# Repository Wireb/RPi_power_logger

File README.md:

# RPi Power Logger
These files are for my Raspberry Pi Zero based power data logger hat. 
 
License is MIT so do what you want with it just don't litigate me. 

Have had quite a few times where I needed actual run times of various battery powered devices. Built this device to collect both the battery voltage, current, and average power as well as up to 8 other voltage rails.

The simple use case is to put channel 0 in line with your battery powered device. This channel is based on the TI INA233 Bidirectional current and power sensor. It supports up to 36Vin and a wide range of currents depending on your choice for R17 and scaling factor. See the INA233 datasheet for more info. In my case of small battery powered devices I have optimized for a max current of 2A. Note the INA233 is set up for high side sensing and the RPi must be powered externally with a common ground with the circuit under test. Once inserted in the power lines just log into the Pi and start the perl script. It will generate a ./Power_data.csv file with all the readings taken every second until you kill the process. 

More advanced setups can use channels 1 - 8 to monitor internal voltage rails. I use this to see which rail is failing first and if any become unstable when the battery voltage is low. Channels 1 - 3 support up to 4V max, channles 4 - 6 support up to 6V max, and channels 7 and 8 support up to 15V max. Note all channels are on a common ground reference.

There is configuration variables in the Perl script for which channels to sample, time between samples, max sample time, and some INA233 configuration. (see Raspbian-Perl directory for more info)

## KiCad
This is a KiCad 5.1.4 project. Both the original KiCad logics, PCB files and a xlsx bill of material can be found here as well as a PDF file of the logics and a top side image of the PCB.   

## Raspbian-Perl
This is the perl script I use to collect the data on the Raspberry Pi. Sample output .csv file of just channel 0 and a processed graph in xlsx format are also included. 

Copyright (c) 2019 Peter Shabino

Permission is hereby granted, free of charge, to any person obtaining a copy of this hardware, software, and associated documentation files 
(the "Product"), to deal in the Product without restriction, including without limitation the rights to use, copy, modify, merge, publish, 
distribute, sublicense, and/or sell copies of the Product, and to permit persons to whom the Product is furnished to do so, subject to the 
following conditions:

The above copyright notice and this permission notice shall be included in all copies or substantial portions of the Product.

THE PRODUCT IS PROVIDED "AS IS", WITHOUT WARRANTY OF ANY KIND, EXPRESS OR IMPLIED, INCLUDING BUT NOT LIMITED TO THE WARRANTIES OF 
MERCHANTABILITY, FITNESS FOR A PARTICULAR PURPOSE AND NONINFRINGEMENT. IN NO EVENT SHALL THE AUTHORS OR COPYRIGHT HOLDERS BE LIABLE 
FOR ANY CLAIM, DAMAGES OR OTHER LIABILITY, WHETHER IN AN ACTION OF CONTRACT, TORT OR OTHERWISE, ARISING FROM, OUT OF OR IN CONNECTION 
WITH THE PRODUCT OR THE USE OR OTHER DEALINGS IN THE PRODUCT.

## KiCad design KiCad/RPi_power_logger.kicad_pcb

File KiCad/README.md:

# KiCad project files
These are KiCad 5.1.4 compatible files. Not going any deeper than that :)

If you just want PCBs now they are available on OSHpark here: 
https://oshpark.com/shared_projects/NPSVbO1J
<a href="https://oshpark.com/shared_projects/NPSVbO1J"></img></a>

## partnumber.csv
CSV file of all unique part numbers. (used for ordering)

## refdes.csv
CSV file of every part by refdes. (used for building)

## RPi_power_logger.xlsx
Bill of Materials in Microsoft Excel format. Includes links to Digikey. 

## RPi_power_logger.pdf
PDF file of logics for easy viewing without KiCad installed. 

## RPi_power_logger_PCB.png
Image file of the top side of the PCB and refdes for easy viewing without KiCad installed. 

Copyright (c) 2019 Peter Shabino

Permission is hereby granted, free of charge, to any person obtaining a copy of this hardware, software, and associated documentation files 
(the "Product"), to deal in the Product without restriction, including without limitation the rights to use, copy, modify, merge, publish, 
distribute, sublicense, and/or sell copies of the Product, and to permit persons to whom the Product is furnished to do so, subject to the 
following conditions:

The above copyright notice and this permission notice shall be included in all copies or substantial portions of the Product.

THE PRODUCT IS PROVIDED "AS IS", WITHOUT WARRANTY OF ANY KIND, EXPRESS OR IMPLIED, INCLUDING BUT NOT LIMITED TO THE WARRANTIES OF 
MERCHANTABILITY, FITNESS FOR A PARTICULAR PURPOSE AND NONINFRINGEMENT. IN NO EVENT SHALL THE AUTHORS OR COPYRIGHT HOLDERS BE LIABLE 
FOR ANY CLAIM, DAMAGES OR OTHER LIABILITY, WHETHER IN AN ACTION OF CONTRACT, TORT OR OTHERWISE, ARISING FROM, OUT OF OR IN CONNECTION 
WITH THE PRODUCT OR THE USE OR OTHER DEALINGS IN THE PRODUCT.

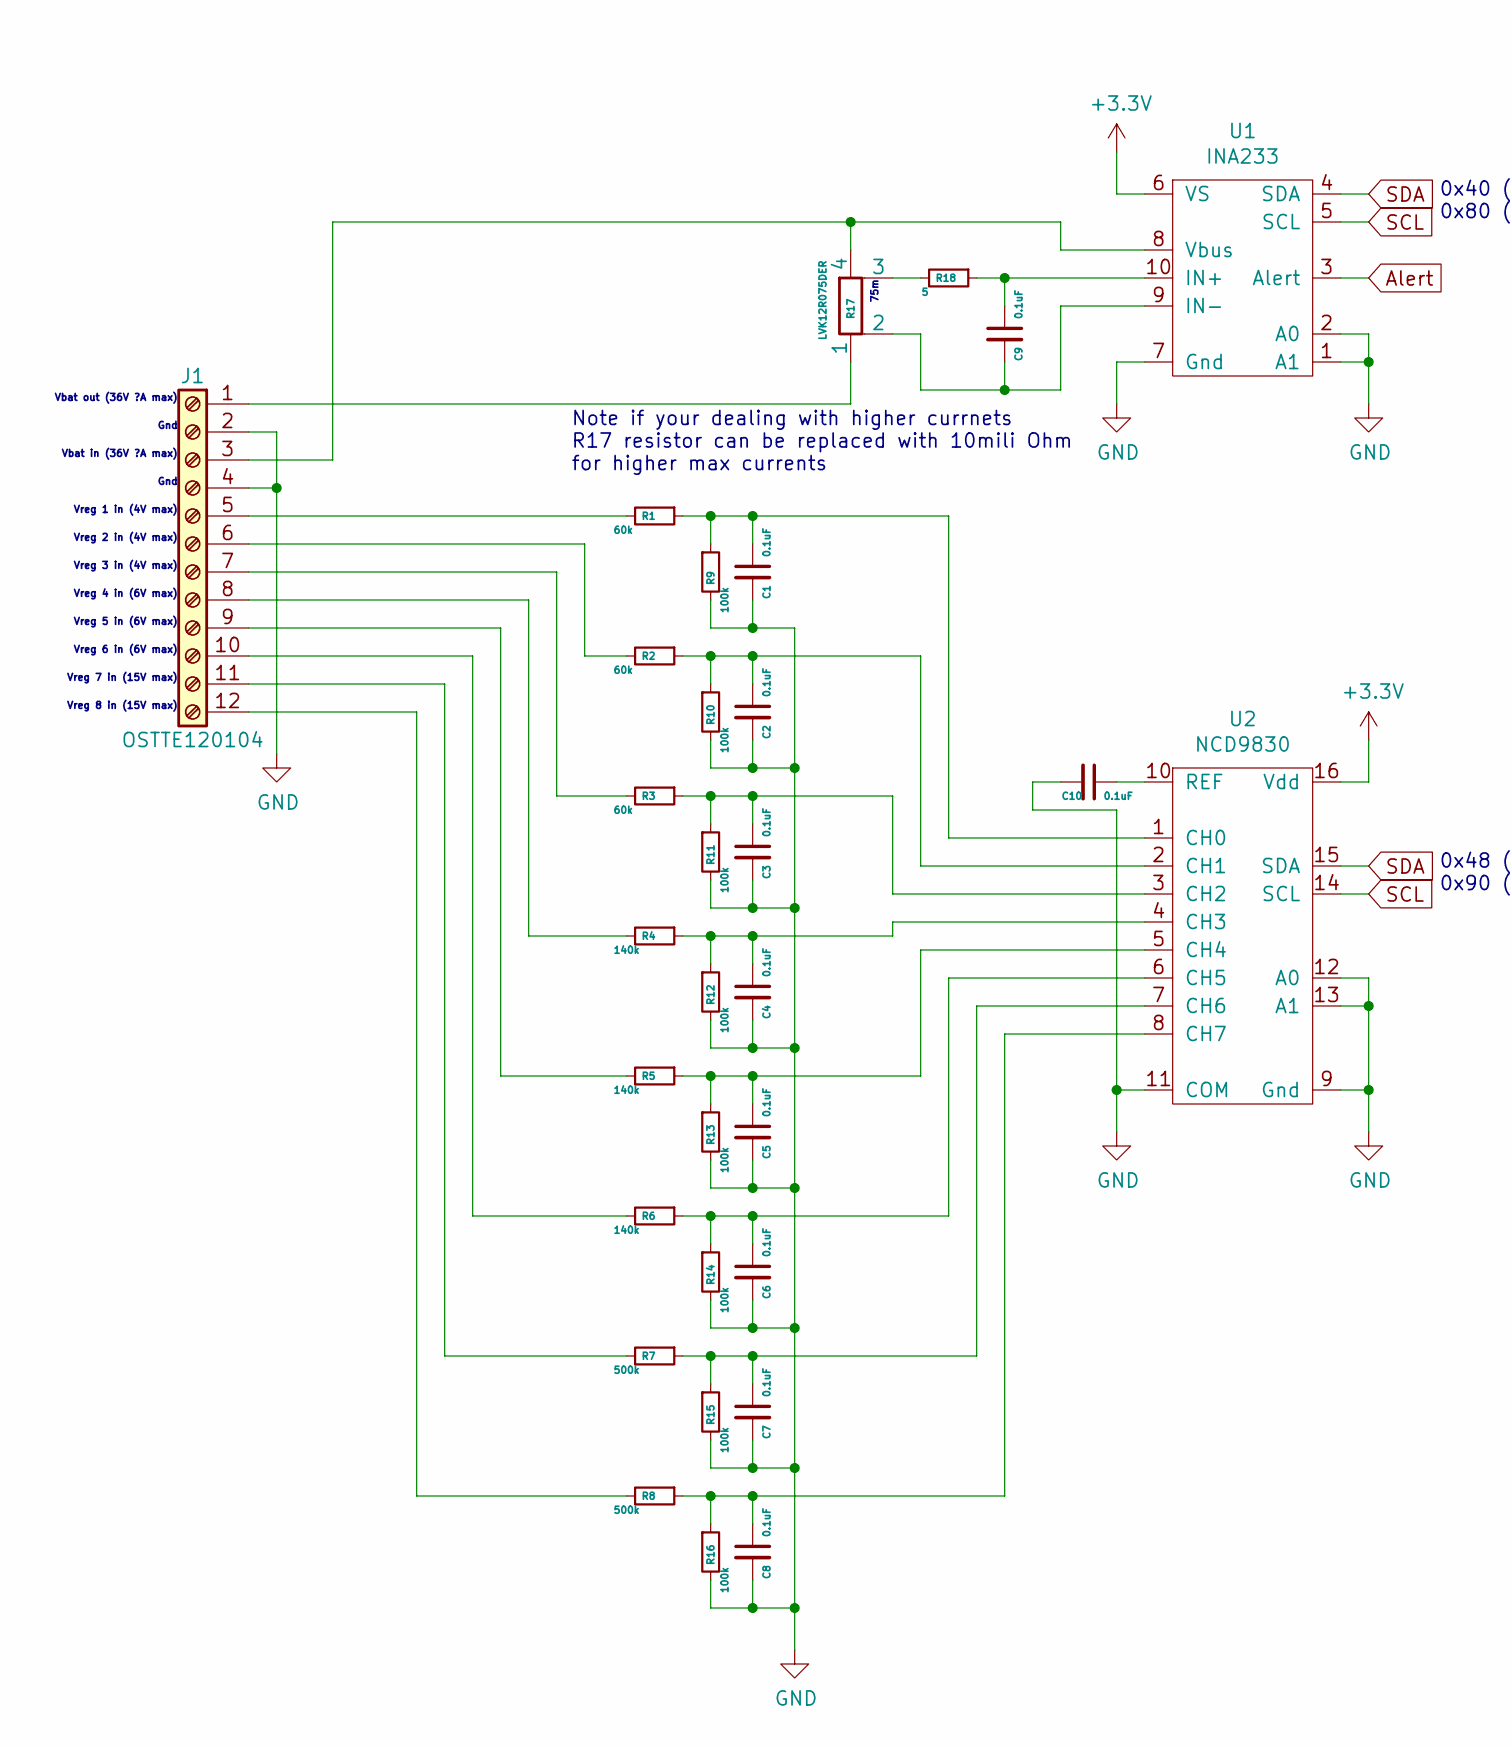
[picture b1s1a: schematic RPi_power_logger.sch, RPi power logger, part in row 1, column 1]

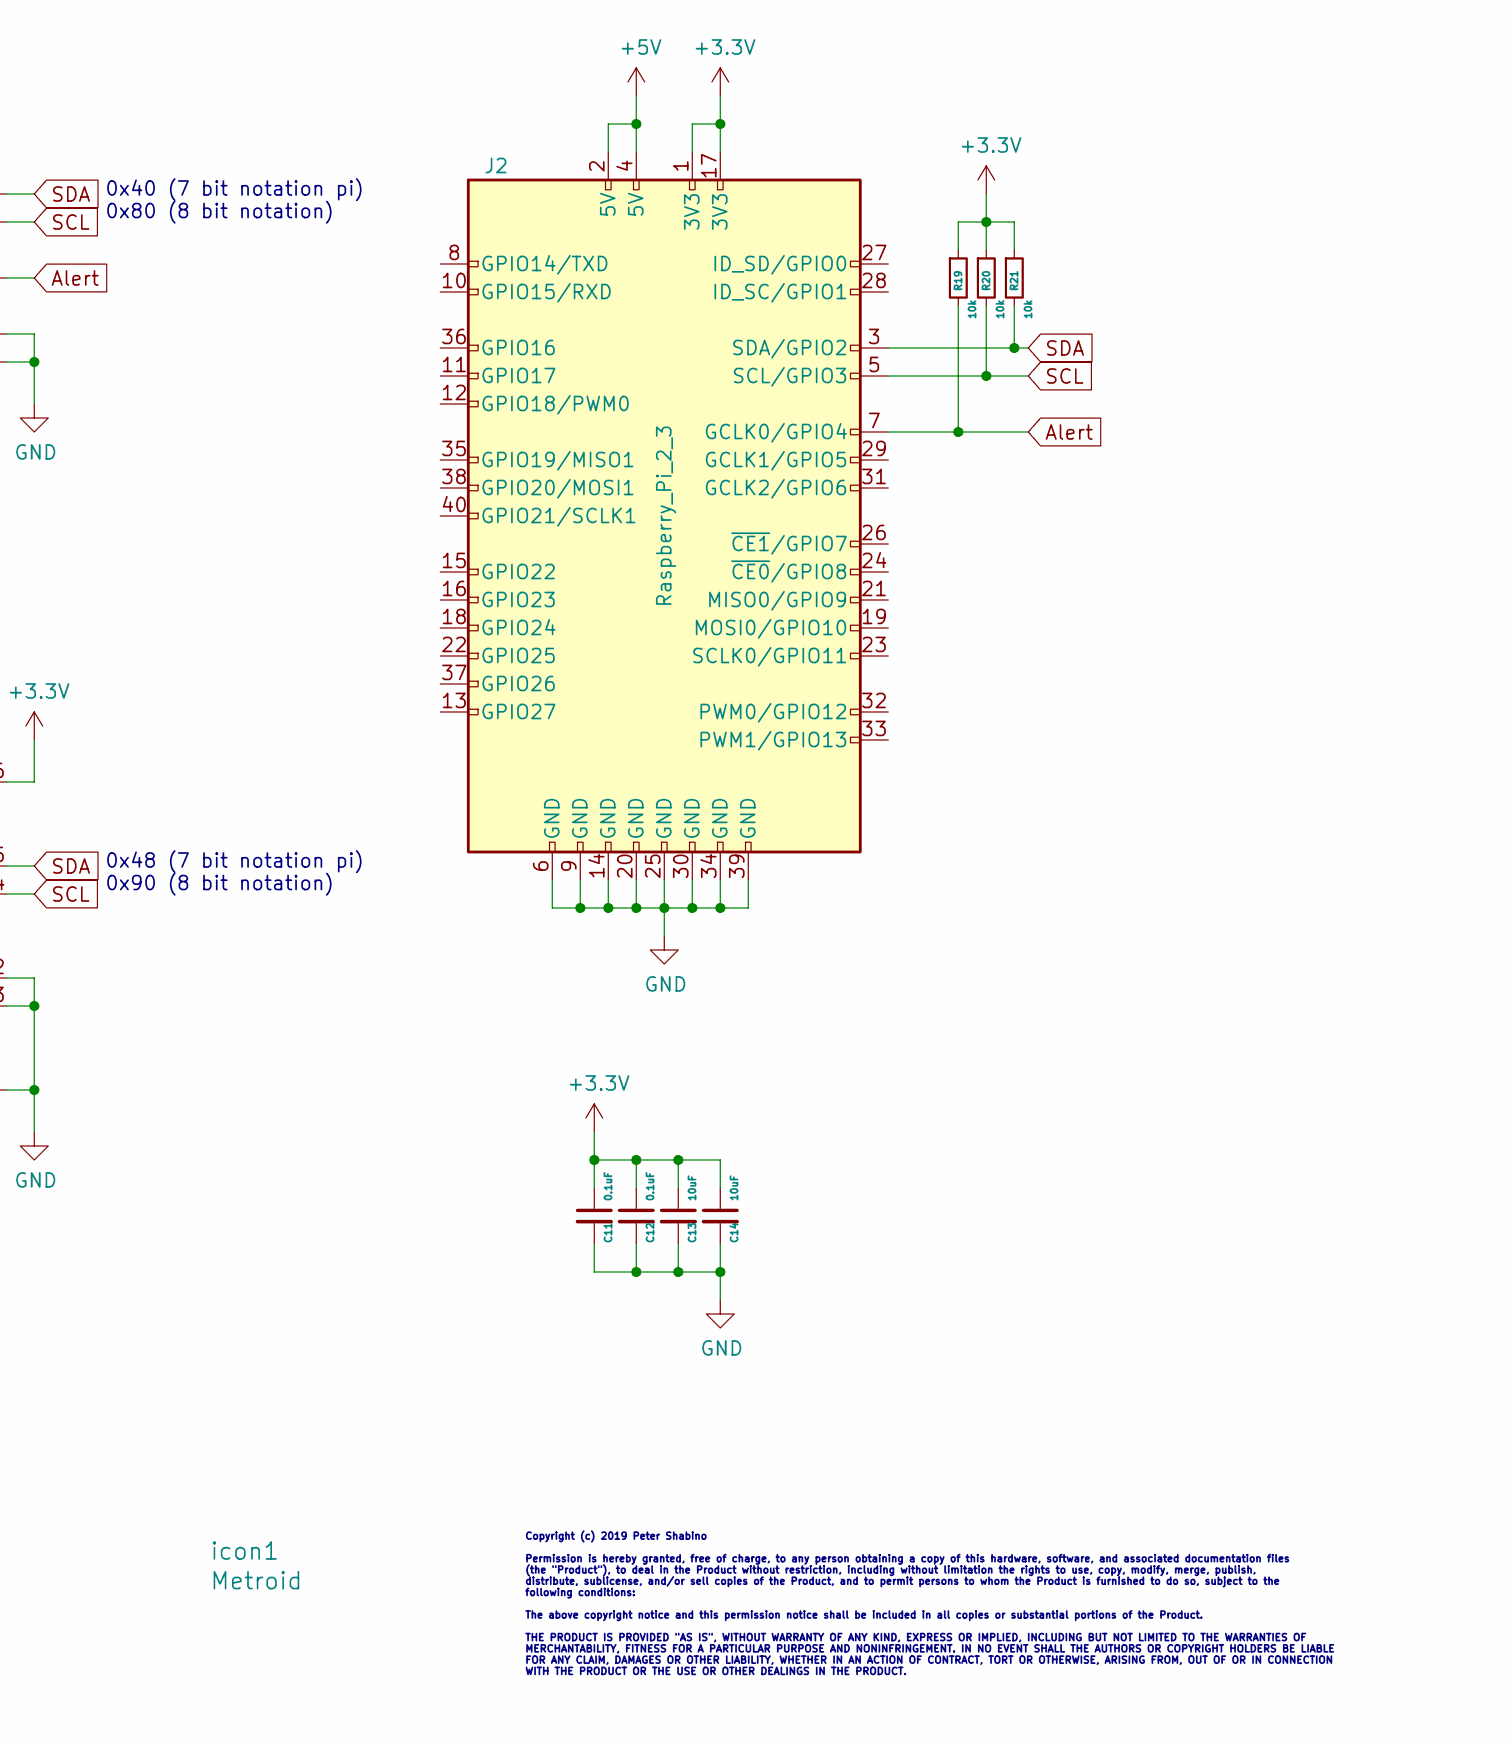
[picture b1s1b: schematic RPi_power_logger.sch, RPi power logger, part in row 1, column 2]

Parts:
C1, C2, C3, C4, C5, C6, C7, C8, C9, C10, C11, C12: 0.1uF; C_0603
C13, C14: 10uF; C_0805
J1: OSTTE120104; TerminalBlock_Phoenix_PT-3.5mm_12pol
J2: Raspberry_Pi_2_3; Pin_Header_Straight_2x20_Pitch2.54mm
R1, R2, R3: 60k; R_0603
R4, R5, R6: 140k; R_0603
R7, R8: 500k; R_0603
R9, R10, R11, R12, R13, R14, R15, R16: 100k; R_0603
R17: LVK12R075DER; LVK12
R18: 5; R_0603
R19, R20, R21: 10k; R_0603
U1: INA233; MSOP-10_W3mm
U2: NCD9830; TSSOP-16_4.4x5mm_Pitch0.65mm
icon1: Metroid; metroid

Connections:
+3V3: C11.1, C12.1, C13.1, C14.1, J2.1 (3V3), J2.17 (3V3), R19.1, R20.1, R21.1, U1.6 (VS), U2.16 (Vdd)
+5V: J2.2 (5V), J2.4 (5V)
Alert: J2.7 (GCLK0/GPIO4), R19.2, U1.3 (Alert)
GND: C1.2, C2.2, C3.2, C4.2, C5.2, C6.2, C7.2, C8.2, C10.2, C11.2, C12.2, C13.2, C14.2, J1.2, J1.4, J2.6 (GND), J2.9 (GND), J2.14 (GND), J2.20 (GND), J2.25 (GND), J2.30 (GND), J2.34 (GND), J2.39 (GND), R9.2, R10.2, R11.2, R12.2, R13.2, R14.2, R15.2, R16.2, U1.1 (A1), U1.2 (A0), U1.7 (Gnd), U2.9 (Gnd), U2.11 (COM), U2.12 (A0), U2.13 (A1)
unnamed: C1.1, R1.1, R9.1, U2.1 (CH0)
unnamed: C2.1, R2.1, R10.1, U2.2 (CH1)
unnamed: C3.1, R3.1, R11.1, U2.3 (CH2)
unnamed: C4.1, R4.1, R12.1, U2.4 (CH3)
unnamed: C5.1, R5.1, R13.1, U2.5 (CH4)
unnamed: C6.1, R6.1, R14.1, U2.6 (CH5)
unnamed: C7.1, R7.1, R15.1, U2.7 (CH6)
unnamed: C8.1, R8.1, R16.1, U2.8 (CH7)
unnamed: C9.1, R18.1, U1.10 (IN+)
unnamed: C9.2, R17.2, U1.9 (IN-)
unnamed: C10.1, U2.10 (REF)
unnamed: J1.1, R17.1
unnamed: J1.3, R17.4, U1.8 (Vbus)
unnamed: J1.5, R1.2
unnamed: J1.6, R2.2
unnamed: J1.7, R3.2
unnamed: J1.8, R4.2
unnamed: J1.9, R5.2
unnamed: J1.10, R6.2
unnamed: J1.11, R7.2
unnamed: J1.12, R8.2
unnamed: R17.3, R18.2
SCL: J2.5 (SCL/GPIO3), R20.2, U1.5 (SCL), U2.14 (SCL)
SDA: J2.3 (SDA/GPIO2), R21.2, U1.4 (SDA), U2.15 (SDA)

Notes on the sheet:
0x40 (7 bit notation pi) 0x80 (8 bit notation)
0x48 (7 bit notation pi) 0x90 (8 bit notation)
Vbat in (36V ?A max)
Gnd
Vbat out (36V ?A max)
Vreg 1 in (4V max)
Vreg 2 in (4V max)
Vreg 3 in (4V max)
Vreg 4 in (6V max)
Vreg 5 in (6V max)
Vreg 6 in (6V max)
Vreg 7 in (15V max)
Vreg 8 in (15V max)
Copyright (c) 2019 Peter Shabino Permission is hereby granted, free of charge, to any person obtaining a copy of this hardware, software, and associated documentation files (the "Product"), to deal in the Product without restriction, including without limitation the rights to use, copy, modify, mer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
75m
Note if your dealing with higher currnets R17 resistor can be replaced with 10mili Ohm for higher max currents

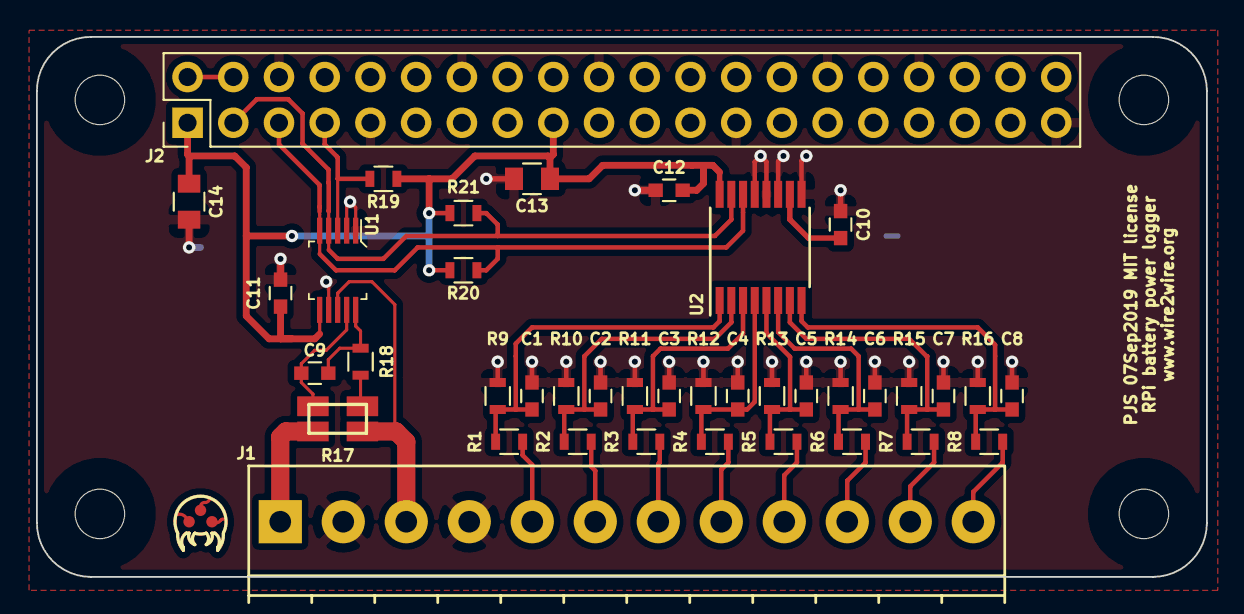
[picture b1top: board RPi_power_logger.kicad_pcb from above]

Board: 2 copper layers, 65.0 x 30.0 mm, 40 parts (0 on the bottom side), 28 nets.

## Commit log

2019-11-26 First push
2019-11-26 formatting fix
2019-11-26 documenation
2019-11-26 link
2019-11-26 links

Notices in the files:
KiCad/RPi_power_logger.kicad_pcb:
PJS 07Sep2019 MIT license
